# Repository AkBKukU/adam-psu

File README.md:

# Coleco Adam Internal PSU

The Coleco Adam originally shipped with a printer that contained the entire PSU 
for the device. It generated 12V, 5V, & -5V DC voltages for the system to run on.
Now it is increasingly difficult to find the printer to go along with the 
system. This renders them unusable.

This project is an internal PSU that can be mounted inside the standalone 
Coleco Adam. If you have an Expansion Module #3 version of the Adam, it can be
used outside of the system as well.

## Installation 

This part was designed specifically to be non-destructive and once you have an
assembled part, does not require any soldering. The DB9 connector on the standalone
Adam is on a small cabled PCB. This board mounts in place of that and you 
internally connect that cable to the new PSU. Optionally, you could cut or 
desolder the DB9 connector and directly bridge across to the available pads.

For use with the Expansion Module #3 version of the Adam, the board can be 
externally plugged into the system. Based on feedback, this is assumed to be 
a much less common model and the design hasn't been optimized for this use. You 
may need to extend the DB9 connection to have enough clearance. A solid DB9
male to female adapter is encouraged over a cable for its better current 
capacity. If you do opt to use a DB9 extension cable **make sure it is not a 
null modem cable!**. Pins 3 & 3 on a null modem cable are swapped which will 
swap 12V and 5V going to your system which will **severely damage** crucial 
components.

## Functionality

This power supply is fundamentally a multi voltage DC-DC regulator. It takes in
a 12V 3A power source and while passing through the 12V also generates 5V and
-5V. The system itself has the following maximum power ratings:

 - 5V - 2.75A
 - -5V - 0.2A
 - 12VI - 0.6A
 - 12VL - 0.3A

(*Taken from page 49 of the Adam Technical reference manual*)

The 12V rail is split between inductive and logic loads on the system side. `D1`
allows for potentially high voltages to be recirculated but due to the shared
ground at this time I'm not sure how useful this really is.

This power supply is capable of supplying the following with the DC-DC 
regulators:

 - 5V - 5A
 - -5V - 1A

These higher output capabilities combined with the ability to change the 12V 
external power source should allow all potential accessories to have sufficient 
power. The original maximum power rating is in total ~25.2W, using a 3A 12V 
AC-DC converter provides ample headroom for DC regulations losses.

## Design

This regulator is made using SMPS Buck regulators to reduce the 12V input to 5V 
and -5V. The -5V source is a standard buck regulators being used in a negative 
configuration. Care has been taken in the design and parts selection to maintain
as much efficiency as possible. Despite this there will be power dissipation 
still and the board layout has taken this into consideration providing large
copper pours where possible. Heat sinking should not be necessary as the parts
should be, on average, drawing less than half of their maximum current in 
addition to the PCB cooling.

The physical parts selection for this as well as the layout design has kept in 
mind the ability to hand solder the parts. However, outside of the I/O, all 
parts are SMD and go down to 0603 sized passives. It is recommend that you have
a solid background in soldering, but this is not an especially difficult SMD 
board to assemble. `U2`, is an SOIC-8 with a thermal pad which will likely be 
the part that will give beginners the most difficulty. Recommended steps are:

 - Lightly tin the thermal pad
 - Apply flux
 - Place the part down, checking orientation
 - Solder opposing corner pins
 - Apply heat to the underside of the board while also applying pressure to the 
   part
 - Finish soldering remaining pins

## Availability, BOM, and Ordering

I will be producing these indefinitely and making them available for purchase.
They will be available on my website once I have assembled and validated the 
design.

The BOM is stored as extra fields in the KiCad schematic and can be exported
from there. It is also included as a CSV file with the non-orderable parts 
removed.

I have also created BOMs on Digi-Key and Mouser as shared carts that you can 
order directly:

Digi-Key: https://www.digikey.com/short/p0tbzh
Mouser: https://www.mouser.com/ProjectManager/ProjectDetail.aspx?AccessID=6486fe3deb 

**BOM Errata**: For v0.1 boards R4 needs to be changed to 1k instead of `0k. 
The BOM carts have not been updated to reflect this yet.

The parts selection vary slightly between vendors. Equivalent performance low
cost parts were selected in each case.

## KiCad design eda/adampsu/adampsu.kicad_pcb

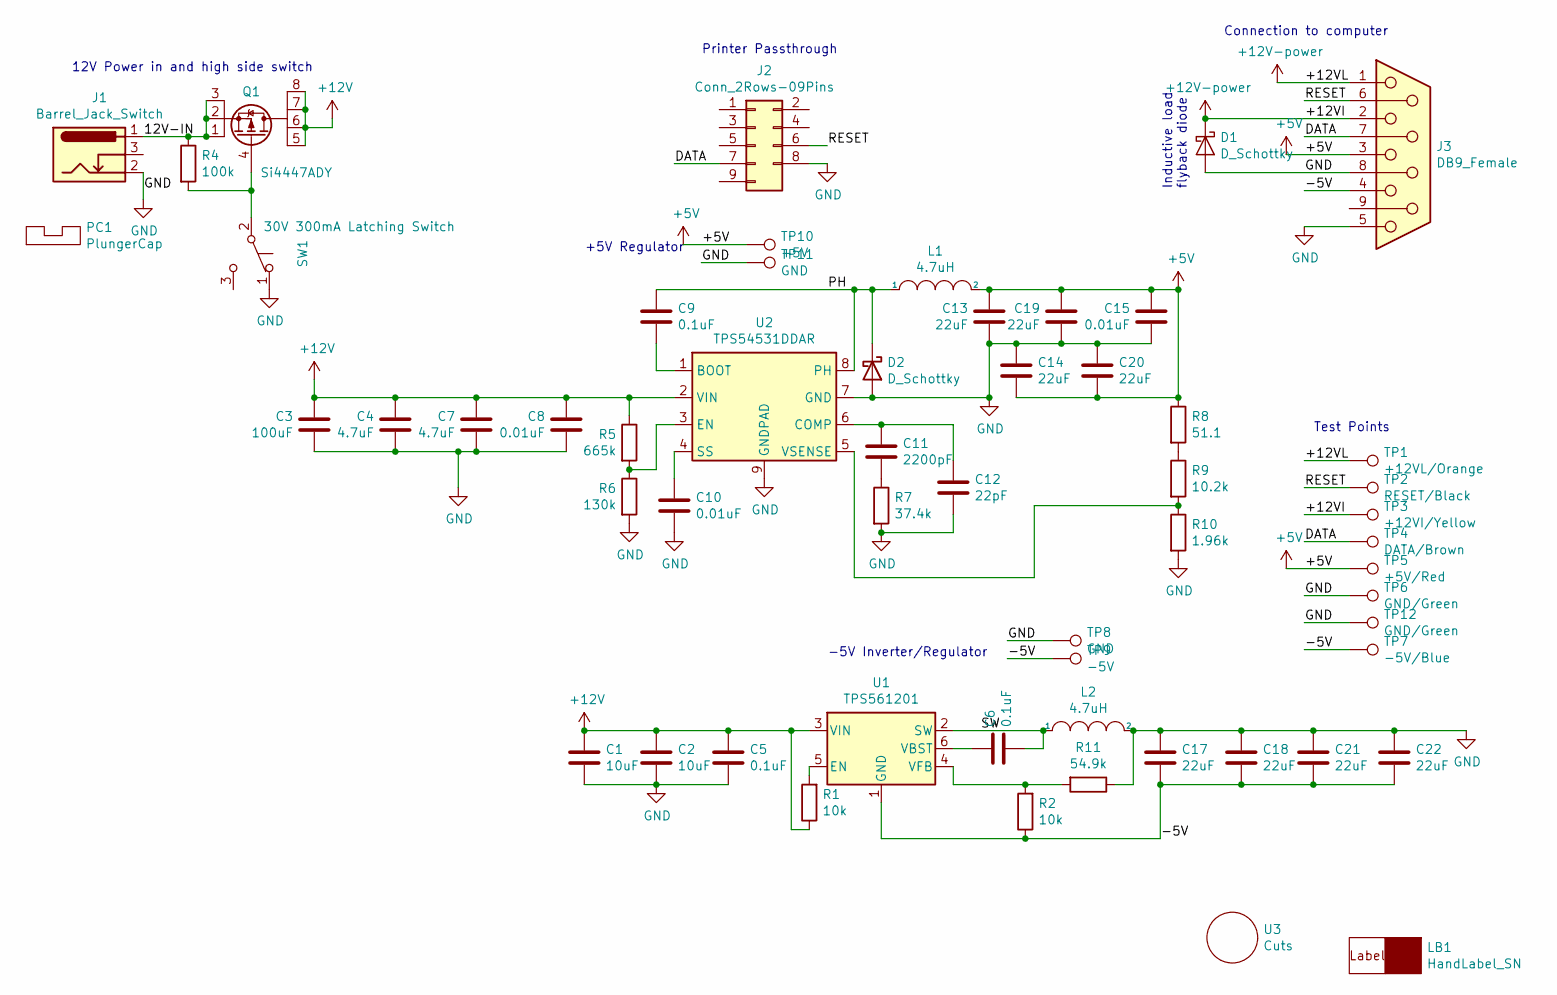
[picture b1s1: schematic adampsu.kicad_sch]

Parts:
C1, C2: 10uF; C_0805_2012Metric_Pad1.15x1.40mm_HandSolder; mouser 81-GRM21BC81C106KE5L
C3: 100uF; CP_EIA-7343-43_Kemet-X_Pad2.25x2.55mm_HandSolder; rating XR7; mouser 581-TAJD107K016TNJV
C4, C7: 4.7uF; C_0805_2012Metric_Pad1.15x1.40mm_HandSolder; rating XR7; mouser 81-GRM21BR71C475KE1L
C5: 0.1uF; C_0603_1608Metric_Pad1.05x0.95mm_HandSolder; rating XR7; mouser 603-CC603KRX7R9BB104
C6, C9: 0.1uF; C_0508_1220Metric_Pad1.40x1.15mm_HandSolder; rating XR7; mouser 81-LLL216R71E104MA1L
C8, C10, C15: 0.01uF; C_0603_1608Metric_Pad1.05x0.95mm_HandSolder; rating XR7; mouser 80-C0603C103M5R
C11: 2200pF; C_0603_1608Metric_Pad1.05x0.95mm_HandSolder; rating XR7; mouser 80-C0603C222K5R7411
C12: 22pF; C_0603_1608Metric_Pad1.05x0.95mm_HandSolder; rating XR7; mouser 581-06035C220JAT2A
C13, C14, C17, C18, C19, C20, C21, C22: 22uF; C_1206_3216Metric_Pad1.42x1.75mm_HandSolder; mouser 963-EMK316ABJ226ML-T
D1, D2: D_Schottky; D_SOD-128; mouser 963-EMK325B7226MM-TR
J1: Barrel_Jack_Switch; BarrelJack_CUI_PJ-047AH_Horizontal; mouser 490-PJ-047AH
J2: Conn_2Rows-09Pins; PinHeader_2x05_P2.54mm_Vertical
J3: DB9_Female; DSUB-9_Female_Vertical_P2.77x2.84mm_MountingHoles; mouser 636-171-009-203L001
L1: 4.7uH; L_11.5x10.3_H4.8; rating 15.5mOhm; mouser 673-PA4342.472NLT
L2: 4.7uH; L_11.5x10.3_H4.8; mouser 673-PA4342.472NLT
LB1: HandLabel_SN; adamlabel
PC1: PlungerCap; PlungerCap-4JWHT; mouser 612-4J-WH
Q1: Si4447ADY; SO-8_3.9x4.9mm_P1.27mm
R1, R2: 10k; R_0603_1608Metric_Pad1.05x0.95mm_HandSolder; mouser 603-RC0603FR-071K96L
R4: 100k; R_0603_1608Metric_Pad1.05x0.95mm_HandSolder
R5: 665k; R_0603_1608Metric_Pad1.05x0.95mm_HandSolder; mouser 603-RC0603FR-07665KL
R6: 130k; R_0603_1608Metric_Pad1.05x0.95mm_HandSolder; mouser 660-RK73B1JTTD134J
R7: 37.4k; R_0603_1608Metric_Pad1.05x0.95mm_HandSolder; mouser 603-RC0603FR-0737K4L
R8: 51.1; R_0603_1608Metric_Pad1.05x0.95mm_HandSolder; mouser 603-RC0603FR-0751R1L
R9: 10.2k; R_0603_1608Metric_Pad1.05x0.95mm_HandSolder; mouser 667-ERJ-3EKF1022V
R10: 1.96k; R_0603_1608Metric_Pad1.05x0.95mm_HandSolder; mouser 603-RC0603FR-071K96L
R11: 54.9k; R_0603_1608Metric_Pad1.05x0.95mm_HandSolder; mouser 603-RC0603FR-0754K9L
SW1: 30V 300mA Latching Switch; Switch-LC1258EENP; mouser 612-LC1258EENP
TP1: +12VL/Orange; TestPoint_Labeled
TP2: RESET/Black; TestPoint_Labeled
TP3: +12VI/Yellow; TestPoint_Labeled
TP4: DATA/Brown; TestPoint_Labeled
TP5: +5V/Red; TestPoint_Labeled
TP6, TP12: GND/Green; TestPoint_Labeled
TP7: -5V/Blue; TestPoint_Labeled
TP8, TP11: GND; TestPoint_Labeled
TP9: -5V; TestPoint_Labeled
TP10: +5V; TestPoint_Labeled
U1: TPS561201; SOT-23-6_Handsoldering; mouser TPS561201DDCR
U2: TPS54531DDAR; TI_SO-PowerPAD-8_ThermalVias; mouser 595-TPS54531DDAR
U3: Cuts; DB9-SpotMount

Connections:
+5V: C13.1, C14.2, C15.1, C19.1, C20.2, J3.3, L1.2, R8.1, TP5.1, TP10.1
/12V-IN: J1.1, Q1.1 (S), Q1.2 (S), Q1.3 (S), R4.1
/-5V: C17.2, C18.2, C21.2, C22.2, J3.4, R2.1, TP7.1, TP9.1, U1.1 (GND)
/DATA: J2.7, J3.7, TP4.1
/PH: C9.1, D2.1 (K), L1.1, U2.8 (PH)
/RESET: J2.6, J3.6, TP2.1
/SW: C6.2, L2.1, U1.2 (SW)
GND: C1.2, C2.2, C3.2, C4.2, C5.2, C7.2, C8.2, C10.2, C12.2, C13.2, C14.1, C15.2, C17.1, C18.1, C19.2, C20.1, C21.1, C22.1, D1.2 (A), D2.2 (A), J1.2, J2.8, J3.5, J3.8, L2.2, R6.2, R7.2, R10.2, R11.1, SW1.1 (A), TP6.1, TP8.1, TP11.1, TP12.1, U2.7 (GND), U2.9 (GNDPAD)
unnamed: C6.1, U1.6 (VBST)
unnamed: C9.2, U2.1 (BOOT)
unnamed: C10.1, U2.4 (SS)
unnamed: C11.1, C12.1, U2.6 (COMP)
unnamed: C11.2, R7.1
unnamed: Q1.4 (G), R4.2, SW1.2 (B)
unnamed: R1.2, U1.5 (EN)
unnamed: R5.2, R6.1, U2.3 (EN)
unnamed: R8.2, R9.1
unnamed: R9.2, R10.1, U2.5 (VSENSE)
unnamed: R2.2, R11.2, U1.4 (VFB)

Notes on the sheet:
+5V Regulator
-5V Inverter/Regulator
Test Points
Inductive load flyback diode
Printer Passthrough
12V Power in and high side switch
Connection to computer

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
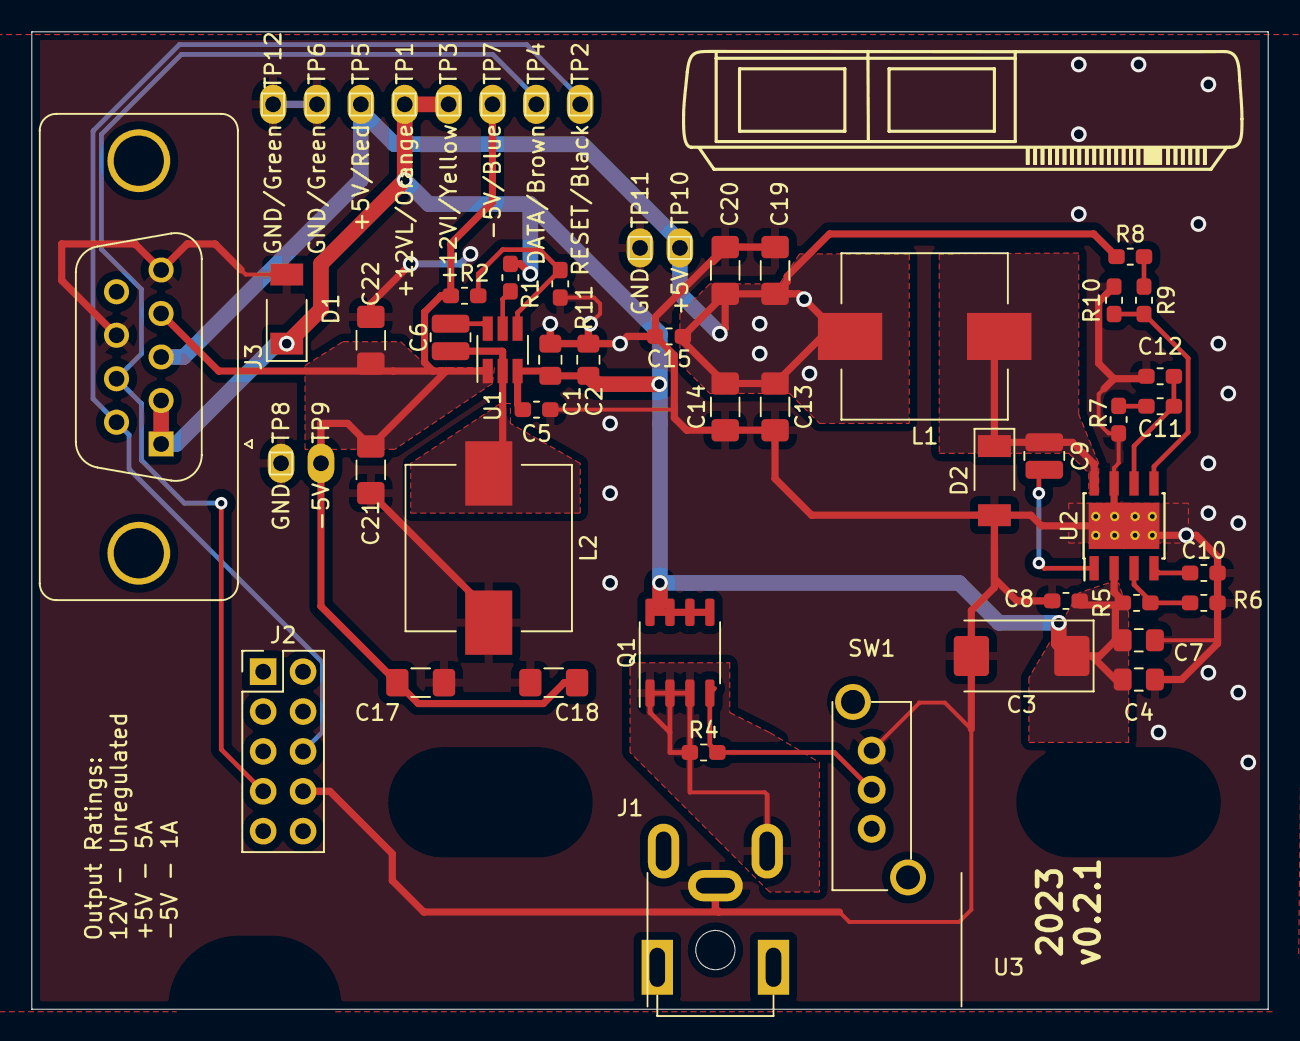
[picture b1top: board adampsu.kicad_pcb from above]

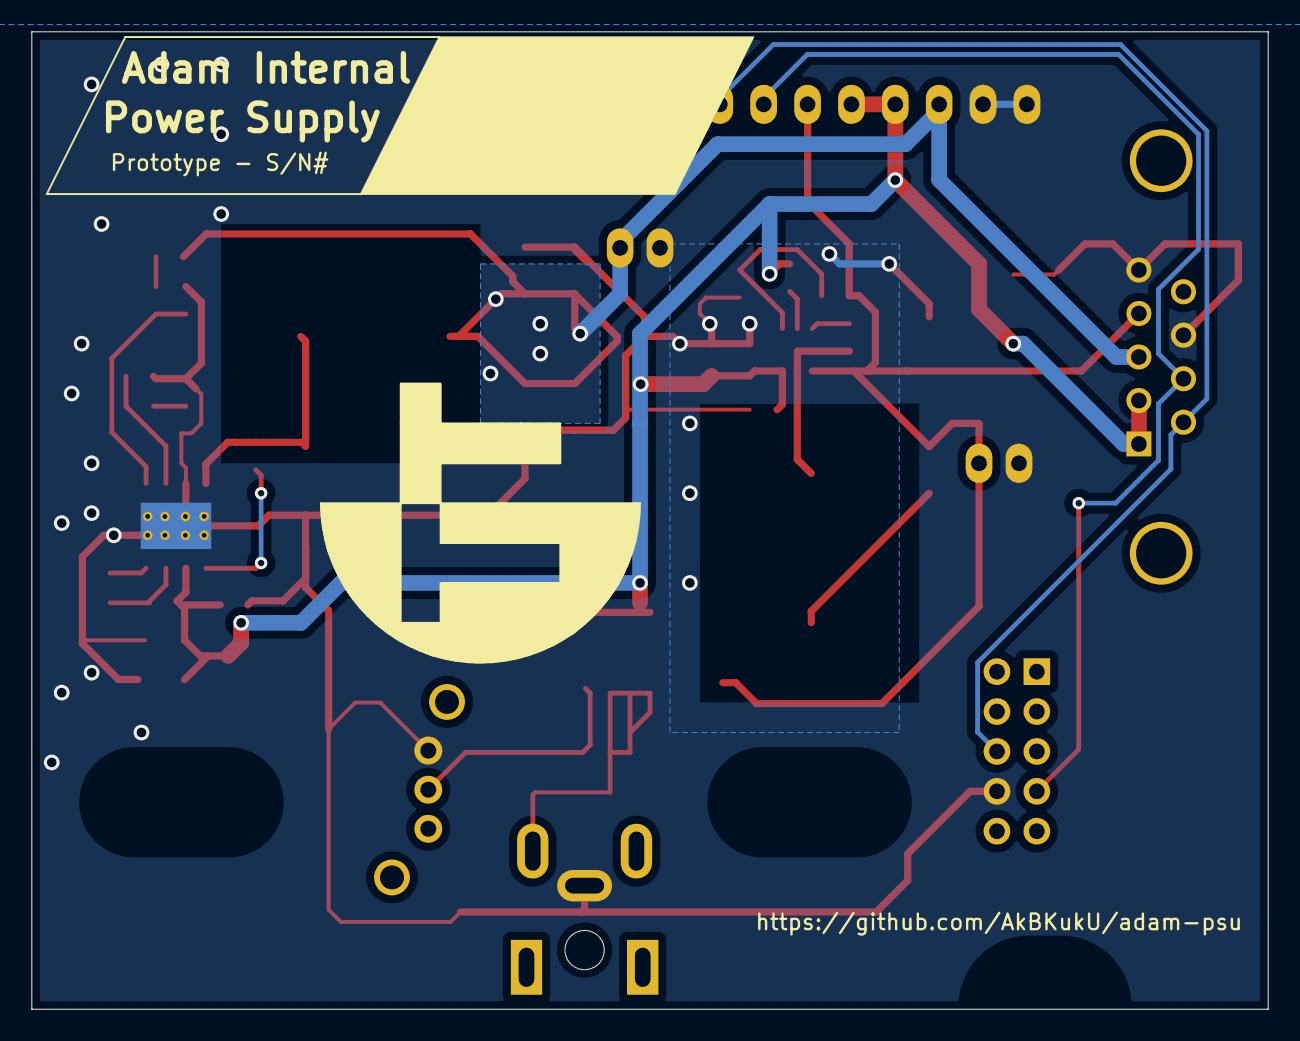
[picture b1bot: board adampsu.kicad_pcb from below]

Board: 2 copper layers, 78.7 x 62.2 mm, 58 parts (2 on the bottom side), 20 nets.

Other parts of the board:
REFe: tt-logo

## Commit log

2019-10-22 Schematic complete
2019-10-27 BOM completeled but using expensive LDO
2019-10-28 switch to buck regulator. Need to choose parts
2019-10-28 Final parts selection finished
2019-10-31 board layout started, but need new -5V regulator
2019-10-31 using non-inverting buck for negative, too expensive though
2019-11-04 Cleanup
2019-11-04 Added readme
2019-11-10 Add board errata after initial assembly.
2019-11-10 Errata update
2019-11-11 Export schematic and PCB to PDFs
2019-11-11 Update README to reflect production errata
2019-11-11 Typo fix
2019-11-11 Update errata
2019-11-12 high side switching
2023-07-16 This is dumb, don't use it. Rewiring top side switch
2023-07-16 Rerouted high side switch to be simpler and exported gerbers.
